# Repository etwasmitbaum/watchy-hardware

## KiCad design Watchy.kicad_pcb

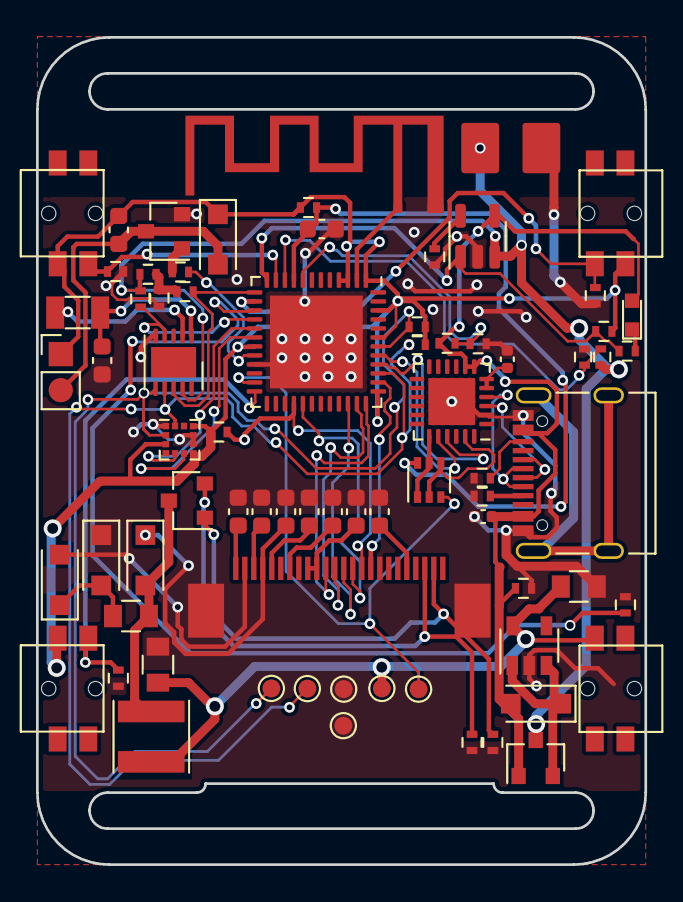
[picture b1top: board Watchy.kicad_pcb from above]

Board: 2 copper layers, 33.8 x 46.0 mm, 74 parts (0 on the bottom side), 55 nets.

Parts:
AE1: SWRA117D
C1, C2, C5, C6, C7, C8, C9, C10: 1uF/50V; C_0603_1608Metric
C3, C4, C12: 4.7uF/50V; C_0805
C11, C13: 4.7uF; C_0402_1005Metric
C14: 100nF; C_0603_1608Metric
C15: 22pF; C_0603_1608Metric
D1, D2, D3, D4: MBR0530; D_SOD-123
D5: LED; LED_0603
D6: 1N4001; D_SOD-123
J1: FPC24(0.5MM); 24_Pins_0.5mm_Pitch_ZIF_Connector_UP
J2: USB_C_Receptacle_USB2.0; USB_C_Receptacle_Palconn_UTC16-G
J4, J5: Conn_01x01; BatteryPads
L1: 10uH 1A; L_Taiyo-Yuden_NR-40xx
M1: Vibration_Motor; Motor_Header
Q1: AO3400A; SOT-23
Q2: UMH3N; SOT-363_SC-70-6
Q4: CJ2301; SOT-23
Q5: S8050; SOT-23
R1, R4, R5, R6, R7, R8, R10, R14, R15, R23: 10K; R_0402
R2, R3: 4.7K; R_0402
R9: 3; R_0402
R11: 680K; R_0402
R12, R13, R19, R20: 100K; R_0402
R16, R17: 1K; R_0402
R18: 220K; R_0402
R21, R22: 5.1k; R_0402
R24: 15k; R_0402
R25: 22k; R_0402
SW1, SW2, SW3, SW4: BTN; K2-1114SA-A4SW-06
TP1: GPIO0; TestPoint_Pad_D1.0mm
TP2: SCL; TestPoint_Pad_D1.0mm
TP3: SDA; TestPoint_Pad_D1.0mm
TP4: 3V3; TestPoint_Pad_D1.0mm
TP5, TP6: GND; TestPoint_Pad_D1.0mm
U1: ESP32-PICO-D4; QFN-48-1EP_7x7mm_P0.5mm_EP5.15x5.15mm
U2: ME6211C33M5G-N; SOT-23-5
U3: CP2102; QFN-24-1EP_4x4mm_P0.5mm_EP2.6x2.6mm
U4: BMA423; LGA-12_2x2mm_P0.5mm
U5: TP4054; SOT-23-5
U6: PCF8563BS; DFN-10-1EP_3x3mm_P0.5mm_EP1.7x2.5mm
Y1: 32.768KHz; Crystal_SMD_3215-2Pin_3.2x1.5mm

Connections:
32KHZ: R19.2, U1.13 (IO33), U6.8 (CLKO)
+3V3: C4.1, C7.1, C12.1, C14.1, D6.1 (K), J1.15, J1.16, L1.2, M1.1 (+), R1.1, R2.1, R3.1, R20.1, R23.2, SW1.2, SW2.1, SW3.1, SW4.1, TP4.1, U1.1 (VDDA), U1.3 (VDDA3P3), U1.4 (VDDA3P3), U1.19 (VDD3P3_RTC), U1.37 (VDD3P3_CPU), U1.43 (VDDA), U1.46 (VDDA), U2.5 (OUT), U4.3 (VDDIO), U4.7 (VDD), U4.10 (CSB)
+BATT: J4.1, Q4.3 (D), R7.1, R11.1, R12.1, U5.3 (VBAT), U6.9 (VDD)
ACC_INT_1: U1.17 (IO14), U4.5 (INT1)
ACC_INT_2: U1.18 (IO12), U4.6 (INT2)
ADC: R12.2, R13.1, U1.10 (IO34)
BATT_STAT: R16.2, R23.1, U1.12 (IO32), U5.1 (STAT)
BTN_1: R4.2, SW1.1, U1.15 (IO26)
BTN_2: R5.2, SW2.2, U1.14 (IO25)
BTN_3: R6.2, SW3.2, U1.11 (IO35)
BTN_4: R10.2, SW4.2, U1.24 (IO4)
BUSY: J1.9, U1.38 (IO19)
DC: J1.11, U1.29 (SD3/IO10)
DTR: Q2.2 (B1), Q2.4 (E2), U3.23 (DTR)
EN: C1.1, Q2.6 (C1), R1.2, U1.9 (EN)
GDR: J1.2, Q1.1 (G), R8.1
GND: AE1.2 (PCB_Trace), C1.2, C2.2, C4.2, C5.2, C6.2, C7.2, C8.2, C9.2, C10.2, C11.1, C12.2, C13.2, C15.2, D2.1 (K), J1.8, J1.17, J2.A1 (GND), J2.A12 (GND), J2.B1 (GND), J2.B12 (GND), J5.1, Q5.2 (E), R4.1, R5.1, R6.1, R8.2, R9.1, R10.1, R13.2, R14.2, R15.1, R18.2, R21.2, R22.2, R25.2, TP5.1, TP6.1, U1.21 (IO15), U1.49 (GND), U2.2 (GND), U3.2 (GND), U3.25 (PAD), U4.1 (SDO), U4.8 (GNDIO), U4.9 (GND), U5.2 (VSS), U6.5 (VSS)
GPIO0: Q2.3 (C2), TP1.1, U1.23 (IO0)
MOSI: J1.14, U1.36 (IO23)
unnamed: AE1.1 (FEED), U1.2 (LNA_IN)
unnamed: C3.1, D1.1 (K), D2.2 (A)
unnamed: C3.2, D3.2 (A), L1.1, Q1.3 (D)
unnamed: D4.1 (K), Q4.2 (S), U2.1 (IN), U2.3 (EN)
unnamed: D5.1 (K), R16.1
unnamed: C14.2, D6.2 (A), M1.2 (-), Q5.3 (C)
unnamed: C2.1, J1.5
unnamed: C6.1, J1.18
unnamed: C8.1, J1.20
unnamed: C9.1, J1.22
unnamed: C10.1, J1.24
unnamed: J2.A5 (CC1), R21.1
unnamed: J2.B5 (CC2), R22.1
unnamed: Q5.1 (B), R17.1
unnamed: R11.2, R18.1, R19.1
unnamed: R24.1, R25.1, U1.8 (SENSOR_VN)
unnamed: J2.A6 (D+), J2.B6 (D+), U3.3 (D+)
unnamed: J2.A7 (D-), J2.B7 (D-), U3.4 (D-)
unnamed: C13.1, U3.5 (VIO), U3.6 (VDD)
unnamed: R15.2, U5.5 (PROG)
unnamed: C15.1, U6.1 (OSCI), Y1.1
unnamed: U6.2 (OSCO), Y1.2
PREVGH: C5.1, D3.1 (K), J1.21
PREVGL: D1.2 (A), J1.23
RES: J1.10, R20.2, U1.28 (SD2/IO9)
RESE: J1.3, Q1.2 (S), R9.2
RTC_INT: R7.2, U1.16 (IO27), U6.4 (~INT)
RTS: Q2.1 (E1), Q2.5 (B2), U3.19 (RTS)
RX: U1.40 (U0RXD/IO3), U3.21 (TXD)
SCK: J1.13, U1.35 (IO18)
SCL: R2.2, TP2.1, U1.39 (IO22), U4.12 (SCX), U6.7 (SCL)
SDA: R3.2, TP3.1, U1.42 (IO21), U4.2 (SDX), U6.6 (SDA)
SS: J1.12, U1.34 (IO5)
TX: U1.41 (U0TXD/IO1), U3.20 (RXD)
VBUS: C11.2, D4.2 (A), D5.2 (A), J2.A4 (VBUS), J2.A9 (VBUS), J2.B4 (VBUS), J2.B9 (VBUS), Q4.1 (G), R14.1, R24.2, U3.7 (REGIN), U3.8 (VBUS), U5.4 (VDD)
VIB_PWM: R17.2, U1.20 (IO13)

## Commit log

2023-07-31 update to kicad 7
2023-08-03 cleanup of USB data lines
2023-08-04 replace micro usb with usb c in schematic
2023-08-04 remove usb c shield connection to ground
2023-08-05 add charging status on gpio pin
2023-08-05 use valid pins for charging on gpio pins
2023-08-06 use watchy footprint for resistors
2023-08-07 add vib_mot footprint, remove all traces, rough positions
2023-08-08 erstes Layout, buttons fehlen
2023-08-08 Gerbers erstellt
2023-08-10 fix: unconnected GNDs
2023-08-10 fix: inconsistent and missing footprints
    May have broken something.
    Also updated the PCB with the new footprints.
2023-08-10 remove net tie
2023-08-10 actually update all footprint
2023-08-11 remove old files
2023-08-12 add most 3d models
2023-08-18 update clearances
2023-09-20 update pcb to suite jlcpcb specs
2023-09-20 replace battery connector with pads
2023-09-20 added gerber
2023-10-05 remove watchy and sqfmi on mask
2023-10-17 change r location
2023-10-19 small fixes
    replaced quarz
    fix button pads
    mounting on display connector is ground
2023-12-16 add trim capacitor
    test points need to be placed
2023-12-16 update schematic for trim capacitor
2024-01-10 fixed flashing issue
    Replaced 100nF enabled cap with 1uF
    re-annotated parts
2024-01-11 mounting pads of display connector to ground
2024-01-11 Revert "mounting pads of display connector to ground"
    This reverts commit e5404d61cc9d6168a15466c32b1fe635e5681ff6.
2024-01-11 Revert "fixed flashing issue"
    This reverts commit 310c791037fab022fc14582fc30034d46f66ed13.
2024-01-11 Revert "update schematic for trim capacitor"
    This reverts commit bc47ff4912a5bf578d20c0e57acb1b5880a0f2bb.
2024-01-11 Revert "add trim capacitor"
    This reverts commit 9f3681e30e2bcc4baaaf6c77db3ed12a4f86397f.
2024-01-11 fixes and improvements
    - move battery pads
    - fix battery footprint
2024-01-11 also save schematic
2024-01-12 Rerouting
    Added testpoints
    Made power traces wider
2024-01-27 moved pull down resistors
2024-01-28 Rev2.0
    New Rev with ESP32-S3 and PCF2131
2024-01-28 Cleanup and connection of I2C test points
2024-01-30 Removed zone under logos
2024-06-01 move display conntector down ~2mm
